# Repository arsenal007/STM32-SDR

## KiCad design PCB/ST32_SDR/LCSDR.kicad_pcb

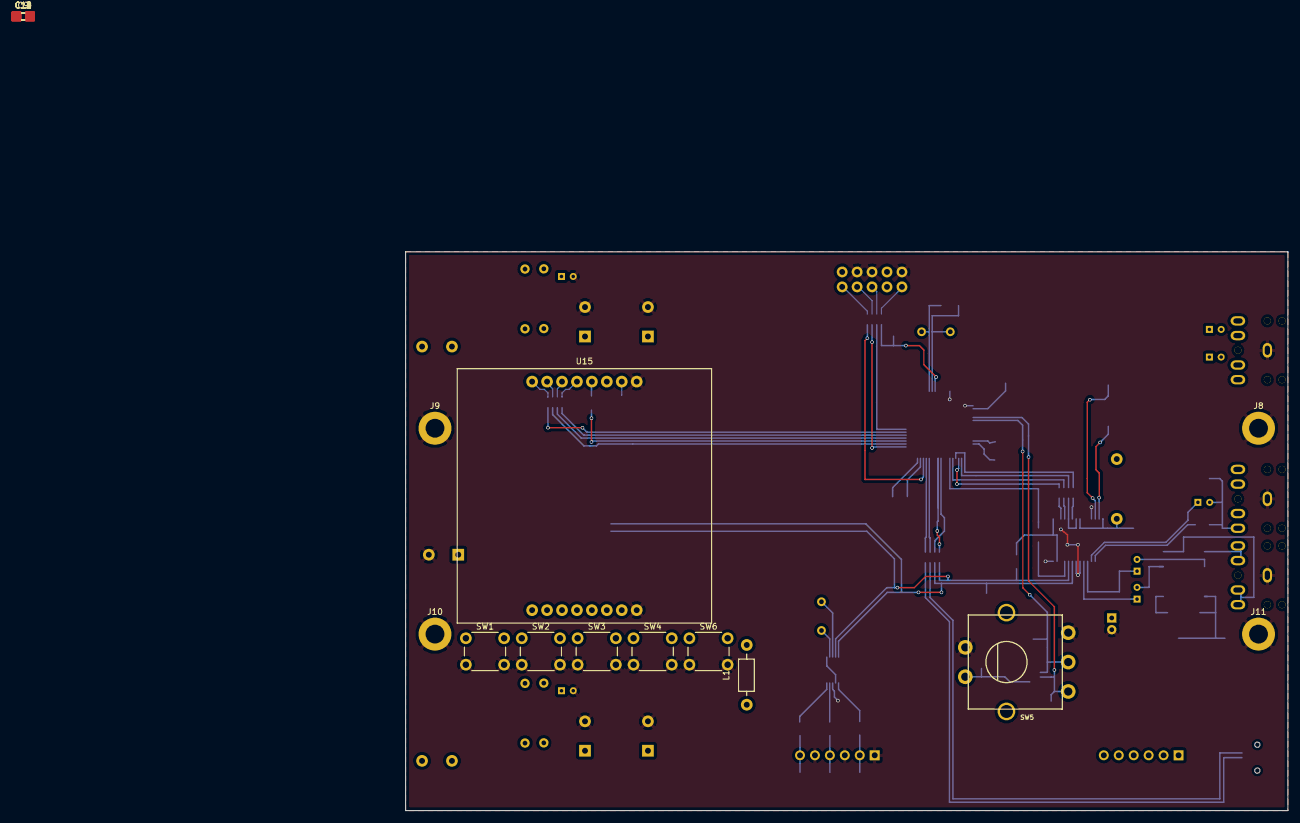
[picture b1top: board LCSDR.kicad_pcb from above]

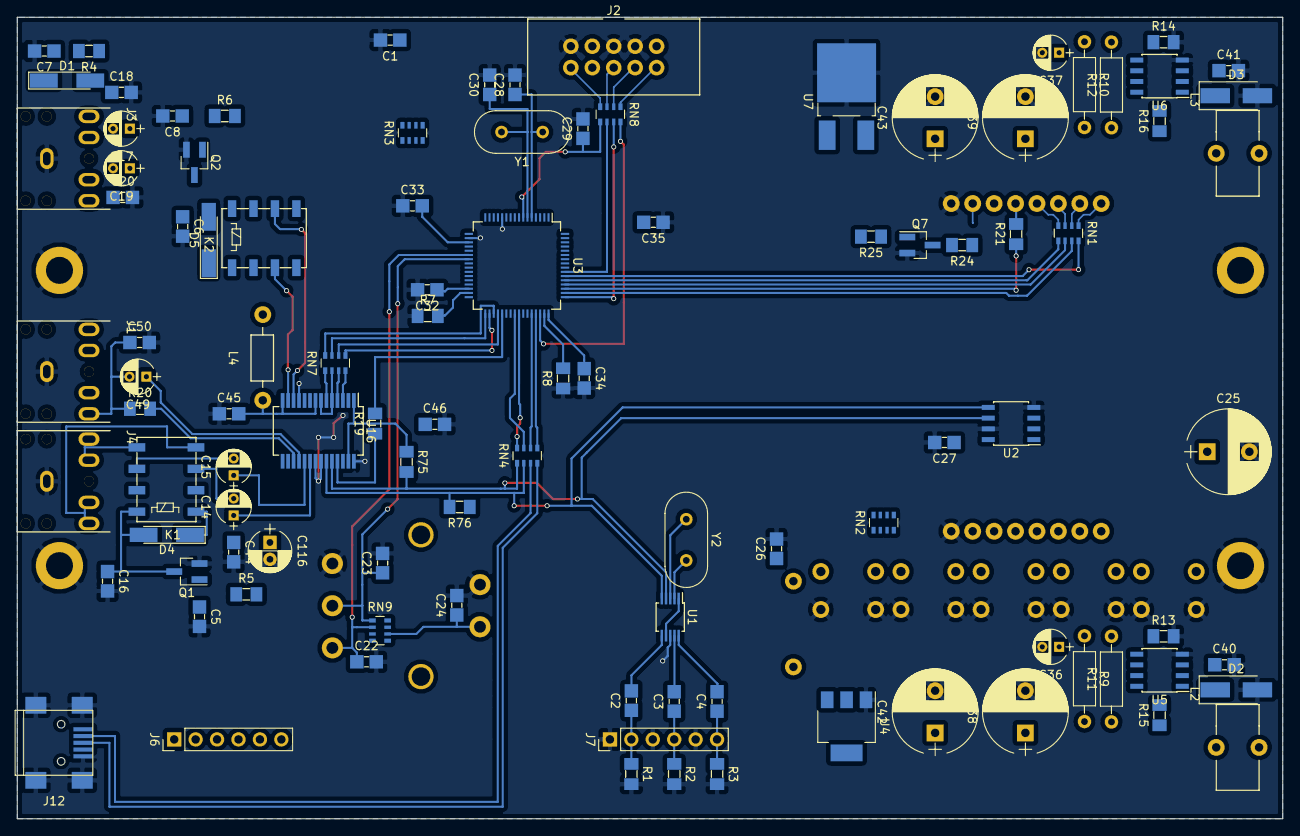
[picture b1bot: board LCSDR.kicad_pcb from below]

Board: 2 copper layers, 150.0 x 95.0 mm, 119 parts (102 on the bottom side), 104 nets.

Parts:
C1, C2, C3, C4, C5, C6, C7, C8, C9, C10, C11, C12, C13, C16, C22, C23, C24, C26, C27, C29, C32, C33, C34, C35, C44, C45, C46: 100nF; C_1206_0603
C14, C15, C17, C19, C49: 1uF; CP_Radial_D4.0mm_P2.00mm
C18, C20: 1nF; C_1206_0603
C25: 330uF; CP_Radial_D10.0mm_P5.00mm
C28, C30: 22; C_1206_0603
C36, C37: 10uF; CP_Radial_D4.0mm_P2.00mm
C38, C39, C42, C43: 1000uF; CP_Radial_D10.0mm_P5.00mm
C40: 200pF; C_1206_0603
C41: 360pF; C_1206_0603
C50: 220; C_1206_0603
C116: 10uF; CP_Radial_D5.0mm_P2.00mm
D1: LL4148; D_MiniMELF_Handsoldering
D2, D3: SS14; D_SMA_Handsoldering
D4, D5: D_Small; D_MiniMELF_Handsoldering
J1: MIC_PTT; audio_jack_3_5mm_PJ307
J2: IDC10 Serial Wire; USBBLASTER
J3: Audio-Jack-3_2Switches; audio_jack_3_5mm_PJ307
J4: LINEIN; audio_jack_3_5mm_PJ307
J6: IQ; Pin_Header_Straight_1x06_Pitch2.54mm
J7: CLK; Pin_Header_Straight_1x06_Pitch2.54mm
J8, J9, J10, J11: Conn_01x01; MountingHole_3.2mm_M3_DIN965_Pad
J12: USB_B_Mini; USB_Mini-B
K1, K2: FRT5; Relay_G6K-2F
L1: 280uH; Choke_Horizontal_RM10mm
L2: 19uH; Choke_Toroid_5x10mm_Vertical
L3: 15uH; Choke_Toroid_5x10mm_Vertical
L4: 100uH; Choke_Horizontal_RM10mm
Q1, Q2: Q_NPN_BEC; SOT-23_Handsoldering
Q7: BC817; SOT-23_Handsoldering
R1, R2, R3, R19: 100; R_1206_0603
R4, R75, R76: 4.7k; R_1206_0603
R5, R6: 2.2k; R_1206_0603
R7, R8: 0*; R_1206_0603
R9, R10, R11, R12: 0.49R; R_Axial_DIN0207_L6.3mm_D2.5mm_P10.16mm_Horizontal
R13: 11k; R_1206_0603
R14: 1k; R_1206_0603
R15: 18k; R_1206_0603
R16: 6.2k; R_1206_0603
R20: 680; R_1206_0603
R21, R24, R25: 56R; R_1206_0603
RN1: 56R; R_Array_Convex_4x0603
RN2, RN9: 4.7k; R_Array_Convex_4x0603
RN3, RN4, RN7, RN8: 47; R_Array_Convex_4x0603
SW1, SW2, SW3, SW4, SW6: SW_Push_Dual; SW_PUSH_6mm_h13mm
SW5: ENCODER; SF-ROTARY-ENCODER
U1: SI5351A; MSOP-10_3x3mm_Pitch0.5mm
U2: FM24CL16B; SOIC-8_3.9x4.9mm_Pitch1.27mm
U3: STM32F401RCTx; LQFP-64_10x10mm_Pitch0.5mm
U4: AP1117-33; SOT-223
U5, U6: MC34063; SOIC-8_3.9x4.9mm_Pitch1.27mm
U7: 78M09; TO-252-2_Rectifier
U15: Nokia_5110_LCD; Nokia_5110-3310_LCD
U16: WM8731_alt; SSOP-28_5.3x10.2mm_Pitch0.65mm
Y1: 20Mhz; Crystal_HC49-U_Vertical
Y2: Crystal; Crystal_HC49-U_Vertical

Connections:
+3V3: C1.1, C25.1, C26.1, C27.1, C33.2, C34.2, C35.2, C38.1, C42.1, C46.1, J2.1, L1.1, L1.2, L2.2, L4.2, R4.1, R15.1, R75.1, R76.1, RN2.5, RN2.6, RN2.7, RN2.8, RN9.3, RN9.7, RN9.8, U1.1, U1.7, U2.8, U3.19, U3.32, U3.48, U3.64, U4.2, U15.6, U16.1, U16.27
+9V: C36.1, C39.1, C43.1, L3.2, R9.1, R11.2, R16.1, U4.3, U5.6, U7.3
+12V: C37.1, D4.1, D5.1, K1.1, K2.1, R10.1, R12.2, U6.6, U7.1
BAND0: RN3.4, U3.8
BAND1: RN3.3, U3.9
BAND2: RN3.2, U3.10
BAND3: RN3.1, U3.11
CLK0: C4.1, J7.6, R3.1
CLK1: C3.1, J7.4, R2.1
CLK2: C2.1, J7.2, R1.1
ENCODER_A: C22.1, RN9.2, SW5.1, U3.22
ENCODER_B: C23.1, RN9.1, SW5.2, U3.23
GND: C1.2, C5.2, C6.2, C7.2, C8.2, C9.2, C10.2, C11.2, C12.2, C13.2, C16.2, C18.2, C20.2, C22.2, C23.2, C24.2, C25.2, C26.2, C27.2, C28.2, C29.2, C30.2, C32.2, C33.1, C34.1, C35.1, C36.2, C37.2, C38.2, C39.2, C40.2, C41.2, C42.2, C43.2, C44.2, C45.1, C46.2, C50.2, C116.2, D2.2, D3.2, J1.3, J2.3, J2.5, J2.9, J3.3, J4.3, J7.1, J7.3, J7.5, J8.1, J9.1, J10.1, J11.1, J12.5, J12.6, Q1.2, Q2.2, Q7.2, R1.2, R2.2, R3.2, R7.1, R8.2, R13.2, R14.2, SW1.2, SW2.2, SW3.2, SW4.2, SW5.3, SW5.5, SW6.2, U1.8, U2.4, U2.7, U3.12, U3.18, U3.60, U3.63, U4.1, U5.4, U6.4, U7.2, U15.8, U16.11, U16.15, U16.21, U16.22, U16.28
I2C_SCL: R75.2, RN4.1, U1.4, U2.6, U16.24
I2C_SCL_MCU: RN4.8, U3.41
I2C_SDA: R76.2, RN4.2, U1.5, U2.5, U16.23
I2C_SDA_MCU: RN4.7, U3.40
I2S_LRCK: RN7.7, U3.33
I2S_MCLK: R19.2, U3.37
I2S_SCLK: RN7.5, U3.34
I2S_SDI: RN7.8, U3.35
I2S_SDO: RN7.6, U3.36
I_IN: J6.1, K1.9
KEY_A: C9.1, RN2.4, SW1.1
KEY_B: C10.1, RN2.3, SW2.1, U3.2
KEY_C: C11.1, RN2.2, SW3.1, U3.3
KEY_D: C12.1, RN2.1, SW4.1, U3.4
KEY_E: C13.1, RN9.5, SW6.1
KEY_MENU: C24.1, RN9.6, SW5.4
LCD_CE: RN1.7, U3.50
LCD_CLK: R21.1, U3.51
LCD_DC: RN1.6, U3.52
LCD_DIN: RN1.5, U3.53
LCD_LIGHT: R25.2, U3.56
LCD_RESET: RN1.8, U3.54
LINE_IN_LEFT: C14.1, U16.20
LINE_IN_RIGHT: C15.1, U16.19
LINE_OUT_LEFT: K2.8, U16.12
LINE_OUT_RIGHT: K2.3, U16.13
MCU_RESET: C29.1, RN8.5, U3.7
MIC_BIAS: R20.2, U16.17
MIC_IN: C49.1, U16.18
unnamed: C2.2, U1.6
unnamed: C3.2, U1.9
unnamed: C4.2, U1.10
unnamed: C5.1, Q1.1, R5.1
unnamed: C6.1, D5.2, K2.10, Q2.3
unnamed: C8.1, Q2.1, R6.1
unnamed: C14.2, K1.3
unnamed: C15.2, K1.8
unnamed: C16.1, D4.2, K1.10, Q1.3
unnamed: C17.1, U16.9
unnamed: C17.2, C18.1, J3.2
unnamed: C19.1, U16.10
unnamed: C19.2, C20.1, J3.1
unnamed: C28.1, U3.5, Y1.1
unnamed: C30.1, U3.6, Y1.2
unnamed: C32.1, U3.30
unnamed: C40.1, U5.3
unnamed: C41.1, U6.3
unnamed: C45.2, L4.1, U16.8, U16.14
unnamed: C49.2, C50.1, J1.1, J1.4, R20.1
unnamed: C44.1, C116.1, U16.16
unnamed: D1.1, J1.2, J1.5
unnamed: D2.1, L2.1, U5.2
unnamed: D3.1, L3.1, U6.2
unnamed: J2.2, RN8.1
unnamed: J2.4, RN8.2
unnamed: J2.6, RN8.3
unnamed: J2.10, RN8.4
unnamed: J4.1, J4.4, K1.4
unnamed: J4.2, J4.5, K1.7
unnamed: J12.2, RN4.3
unnamed: J12.3, RN4.4
unnamed: Q7.1, R25.1
unnamed: Q7.3, R24.2
unnamed: R7.2, U3.31
unnamed: R8.1, U3.47
unnamed: R10.2, R12.1, U6.1, U6.7, U6.8
unnamed: R9.2, R11.1, U5.1, U5.7, U5.8
unnamed: R13.1, R15.2, U5.5
unnamed: R14.1, R16.2, U6.5
unnamed: R19.1, U16.25
unnamed: R21.2, U15.5
unnamed: R24.1, U15.7
unnamed: RN1.1, U15.1
unnamed: RN1.2, U15.2
unnamed: RN1.3, U15.3
unnamed: RN1.4, U15.4
unnamed: RN7.1, U16.6
unnamed: RN7.2, U16.5, U16.7
unnamed: RN7.3, U16.4
unnamed: RN7.4, U16.3
unnamed: U1.2, Y2.2
unnamed: U1.3, Y2.1
PTT_IN: C7.1, D1.2, R4.2
Q_IN: J6.2, K1.2
SWCLK: RN8.7, U3.49
SWDIO: RN8.8, U3.46
SWO: RN8.6, U3.55
TX1: R6.2, U3.21
TX2: R5.2, U3.39
USB_DM: RN4.6, U3.44
USB_DP: RN4.5, U3.45

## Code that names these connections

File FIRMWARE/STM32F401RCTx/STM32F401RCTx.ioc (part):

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Mcu.Name=STM32F401R(B-C)Tx
Mcu.Package=LQFP64
Mcu.UserName=STM32F401RCTx
PA11.Mode=Device_Only
PA11.Signal=USB_OTG_FS_DM
PA12.Mode=Device_Only
PA12.Signal=USB_OTG_FS_DP
PA13.Mode=Trace_Asynchronous_SW
PA13.Signal=SYS_JTMS-SWDIO
PA14.Mode=Trace_Asynchronous_SW
PA14.Signal=SYS_JTCK-SWCLK
PA15.GPIOParameters=GPIO_Label
PA15.GPIO_Label=LCD_CE
PA15.Mode=NSS_Signal_Hard_Output
PA15.Signal=SPI3_NSS
PA8.Mode=I2C
PA8.Signal=I2C3_SCL
PB12.Mode=Full_Duplex_Master
PB12.Signal=I2S2_WS
PB13.Mode=Full_Duplex_Master
PB13.Signal=I2S2_CK
PB14.Mode=Full_Duplex_Master
PB14.Signal=I2S2_ext_SD
PB15.Mode=Full_Duplex_Master
PB15.Signal=I2S2_SD
PB3.Mode=Trace_Asynchronous_SW
PB3.Signal=SYS_JTDO-SWO
PB4.GPIOParameters=GPIO_Label
PB4.GPIO_Label=LCD_LIGHT
PB4.Signal=GPIO_Output
PC10.GPIOParameters=GPIO_Label
PC10.GPIO_Label=LCD_CLK
PC10.Mode=TX_Only_Simplex_Unidirect_Master
PC10.Signal=SPI3_SCK
PC11.GPIOParameters=GPIO_Label
PC11.GPIO_Label=LCD_DC
PC11.Signal=GPIO_Output
PC12.GPIOParameters=GPIO_Label
PC12.GPIO_Label=LCD_DIN
PC12.Mode=TX_Only_Simplex_Unidirect_Master
PC12.Signal=SPI3_MOSI
PC13-ANTI_TAMP.GPIOParameters=GPIO_PuPd,GPIO_Label
PC13-ANTI_TAMP.GPIO_Label=KEY_B
PC13-ANTI_TAMP.GPIO_PuPd=GPIO_PULLDOWN
PC13-ANTI_TAMP.Signal=GPXTI13
PC14-OSC32_IN.GPIOParameters=GPIO_PuPd,GPIO_Label
PC14-OSC32_IN.GPIO_Label=KEY_C
PC14-OSC32_IN.GPIO_PuPd=GPIO_PULLDOWN
PC14-OSC32_IN.Signal=GPXTI14
PC15-OSC32_OUT.GPIOParameters=GPIO_PuPd,GPIO_Label
PC15-OSC32_OUT.GPIO_Label=KEY_D
PC15-OSC32_OUT.GPIO_PuPd=GPIO_PULLDOWN
PC15-OSC32_OUT.Signal=GPXTI15
PC6.Mode=Master_Clock_Activated
PC6.Signal=I2S2_MCK
PC9.Mode=I2C
PC9.Signal=I2C3_SDA
PD2.GPIOParameters=GPIO_Label
PD2.GPIO_Label=LCD_RESET
PD2.Signal=GPIO_Output
PH0\ -\ OSC_IN.Mode=HSE-External-Oscillator
PH0\ -\ OSC_IN.Signal=RCC_OSC_IN
PH1\ -\ OSC_OUT.Mode=HSE-External-Oscillator
PH1\ -\ OSC_OUT.Signal=RCC_OSC_OUT
RCC.HSE_VALUE=20000000
RCC.SYSCLKFreq_VALUE=84000000
RCC.SYSCLKSource=RCC_SYSCLKSOURCE_PLLCLK
board=custom

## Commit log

2019-11-20 add PCB
2019-11-20 add STM32CubeIDE Projects STM32F401RCTx,STM32F405RGx
2019-11-21 add SPI in CubeMX project, add FRAM CPU PCB Project
2019-11-23 Schematics update
2019-11-23 MCU schematics updated LCD Interface
2019-11-24 add display, UI
2019-11-24 recover LCD interface at MCU
2019-11-24 fix MCU
2019-11-24 add LCD resistors
2019-11-28 update schematics
2019-11-29 begin PCB
2019-11-30 LCD at SPI3
2019-11-30 PCB update
2019-11-30 schematics update to privious commit
2019-12-01 PCB Windows 1
2019-12-01 Fix previous commit
2019-12-01 UI PCB linux 1
2019-12-03 PCB Linux 2, update AUDIO_OUT
